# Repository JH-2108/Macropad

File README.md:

# Macropad

A custom 9-key macropad built from scratch using KiCad, featuring a Seeed Studio XIAO microcontroller and a 0.91" OLED display.

## Features

* 9 mechanical keys
* 0.91" OLED display
* Seeed Studio XIAO microcontroller
* USB-C connectivity
* Programmable keys for shortcuts, macros, and other functions
* Designed as a custom DIY hardware project

## Screenshots of my Hackpad 
**My Overall Hackpad**

**Schematics**

**PCB Design**

**Connecting the Case and PCB**

## Challenges 
During the entire design process, I did not face as many challenges as one would being a beginner to creating a Hackpad, before I started this project, I already had the basic understanding of how Fusion360 works, the only thing I needed to master and know are how to created the PCB and the firmware for my Hackpad to successfully function. In order to solve this issue, I went online; searched for tutorials, asked my friend who has a deep sense of love in coding and programming; through these resources, I was able to fully finish designing my Hackpad. For beginners reading this, I believe that you are able to make one too, just like I did!!! 

## BOM
This is everything that you should prepare in order to make this Hackpad

| Component               | Quantity |
| ----------------------- | -------: |
| Seeed Studio XIAO       |        1 |
| Mechanical key switches |        9 |
| Keycaps                 |        9 |
| 0.91" OLED display      |        1 |
| Custom PCB              |        1 |
| USB-C connection        |        1 |

## Repository Structure

```text
macropad/
├── README.md
├── PCB/
│   ├── macropad.kicad_pro
│   ├── macropad.kicad_sch
│   ├── macropad.kicad_pcb
├── CAD files/
│   ├─ base
│   ├─ plate 
├── images/
└── LICENSE
```

## Firmware

The firmware will control the macropad's keys and OLED display.

Planned functionality includes:

* Custom key mappings
* Keyboard shortcuts
* Macro support
* OLED status display
* Future customizable profiles

## Tools

* [KiCad](https://www.kicad.org/) — PCB and schematic design
* Arduino / PlatformIO — Firmware development
* GitHub — Version control and project documentation

## License

This project is open source. See the [LICENSE](LICENSE) file for details.

## Credits

Designed and built by **JH** as a personal hardware and electronics project(and tool)!

---

If you find this project interesting, feel free to take inspiration from it!!! :)

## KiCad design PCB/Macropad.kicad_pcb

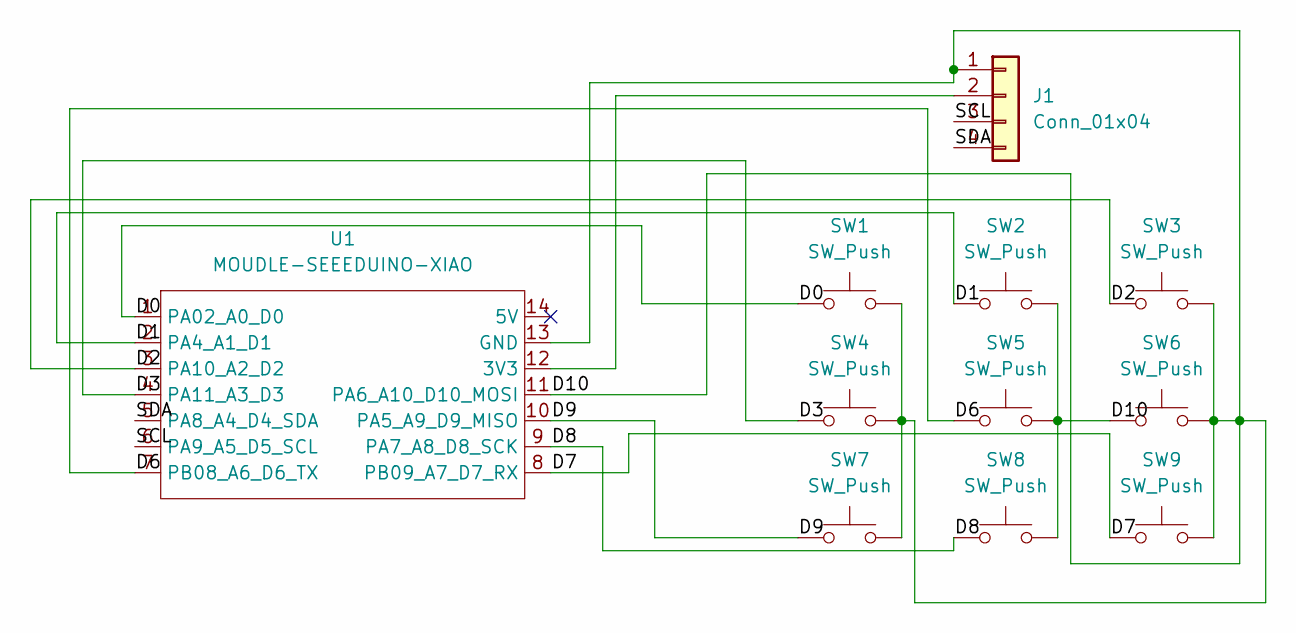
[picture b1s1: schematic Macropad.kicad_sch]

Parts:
J1: Conn_01x04; SSD1306-0.91-OLED-4pin-128x32
SW1, SW2, SW3, SW4, SW5, SW6, SW7, SW8, SW9: SW_Push; SW_Cherry_MX_1.00u_PCB
U1: MOUDLE-SEEEDUINO-XIAO; XIAO-Generic-Hybrid-14P-2.54-21X17.8MM

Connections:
/D0: SW1.1, U1.1 (PA02_A0_D0)
/D1: SW2.1, U1.2 (PA4_A1_D1)
/D2: SW3.1, U1.3 (PA10_A2_D2)
/D3: SW4.1, U1.4 (PA11_A3_D3)
/D6: SW5.1, U1.7 (PB08_A6_D6_TX)
/D7: SW9.1, U1.8 (PB09_A7_D7_RX)
/D8: SW8.1, U1.9 (PA7_A8_D8_SCK)
/D9: SW7.1, U1.10 (PA5_A9_D9_MISO)
/D10: J1.1, SW1.2, SW2.2, SW3.2, SW4.2, SW5.2, SW6.1, SW6.2, SW7.2, SW8.2, SW9.2, U1.11 (PA6_A10_D10_MOSI), U1.13 (GND)
/SCL: J1.3, U1.6 (PA9_A5_D5_SCL)
/SDA: J1.4, U1.5 (PA8_A4_D4_SDA)
unnamed: J1.2, U1.12 (3V3)

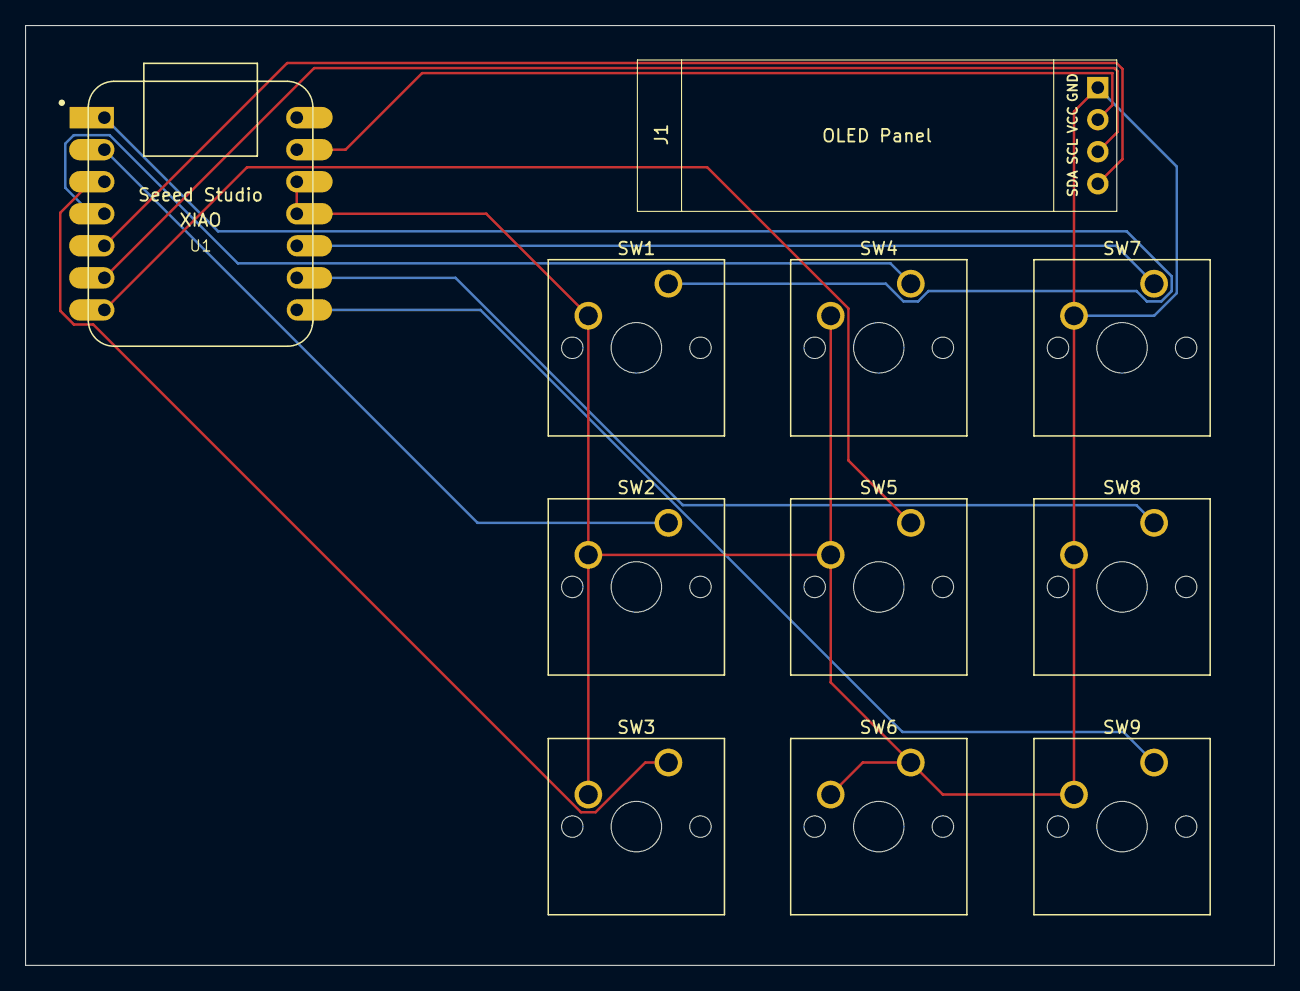
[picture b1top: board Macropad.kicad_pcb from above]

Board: 2 copper layers, 99.0 x 74.5 mm, 11 parts (0 on the bottom side), 12 nets.
